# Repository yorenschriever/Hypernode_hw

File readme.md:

# HyperNode

HyperNode is a distribution node for 
[Hyperion](https://github.com/yorenschriever/Hyperion2). You can use this device to connect up to 8 led strips and 1 DMX universe. 

The device is based on the WT32-ETH01. The pcbs are made with AutoDesk Eagle. 

# BOM

|Amount|Name|Type|Value|Size|Price|Link|
|-|-|-|-|-|-|-|
|1|Controller||WT32-ETH01||||
|1|Line driver||74HCT245D|SO20W||
|1|DMX transceiver|MAX488||SOIC-8||
|2|Decoupling capacitor|Ceramic capacitor|100 nF|0603||
|10|Protection resistor|Thin film resistor|100 Ohm|0603||
|3|RJ45 Connectors|||||
|2|Resistor for led|Resistor|180 Ohm|0603|||
|2|Status and power led|SMD LED|Red|0603|||
|1|Power supply cap|Tantalum Capacitor|470 uF|D Type||
|1|Rectifier diode|||SMB||
|1|Step down module|||||
|1|JST XH connector M+F|2 Pin||||
|1|DC Barrel connector|2.1 x 5.5mm||||

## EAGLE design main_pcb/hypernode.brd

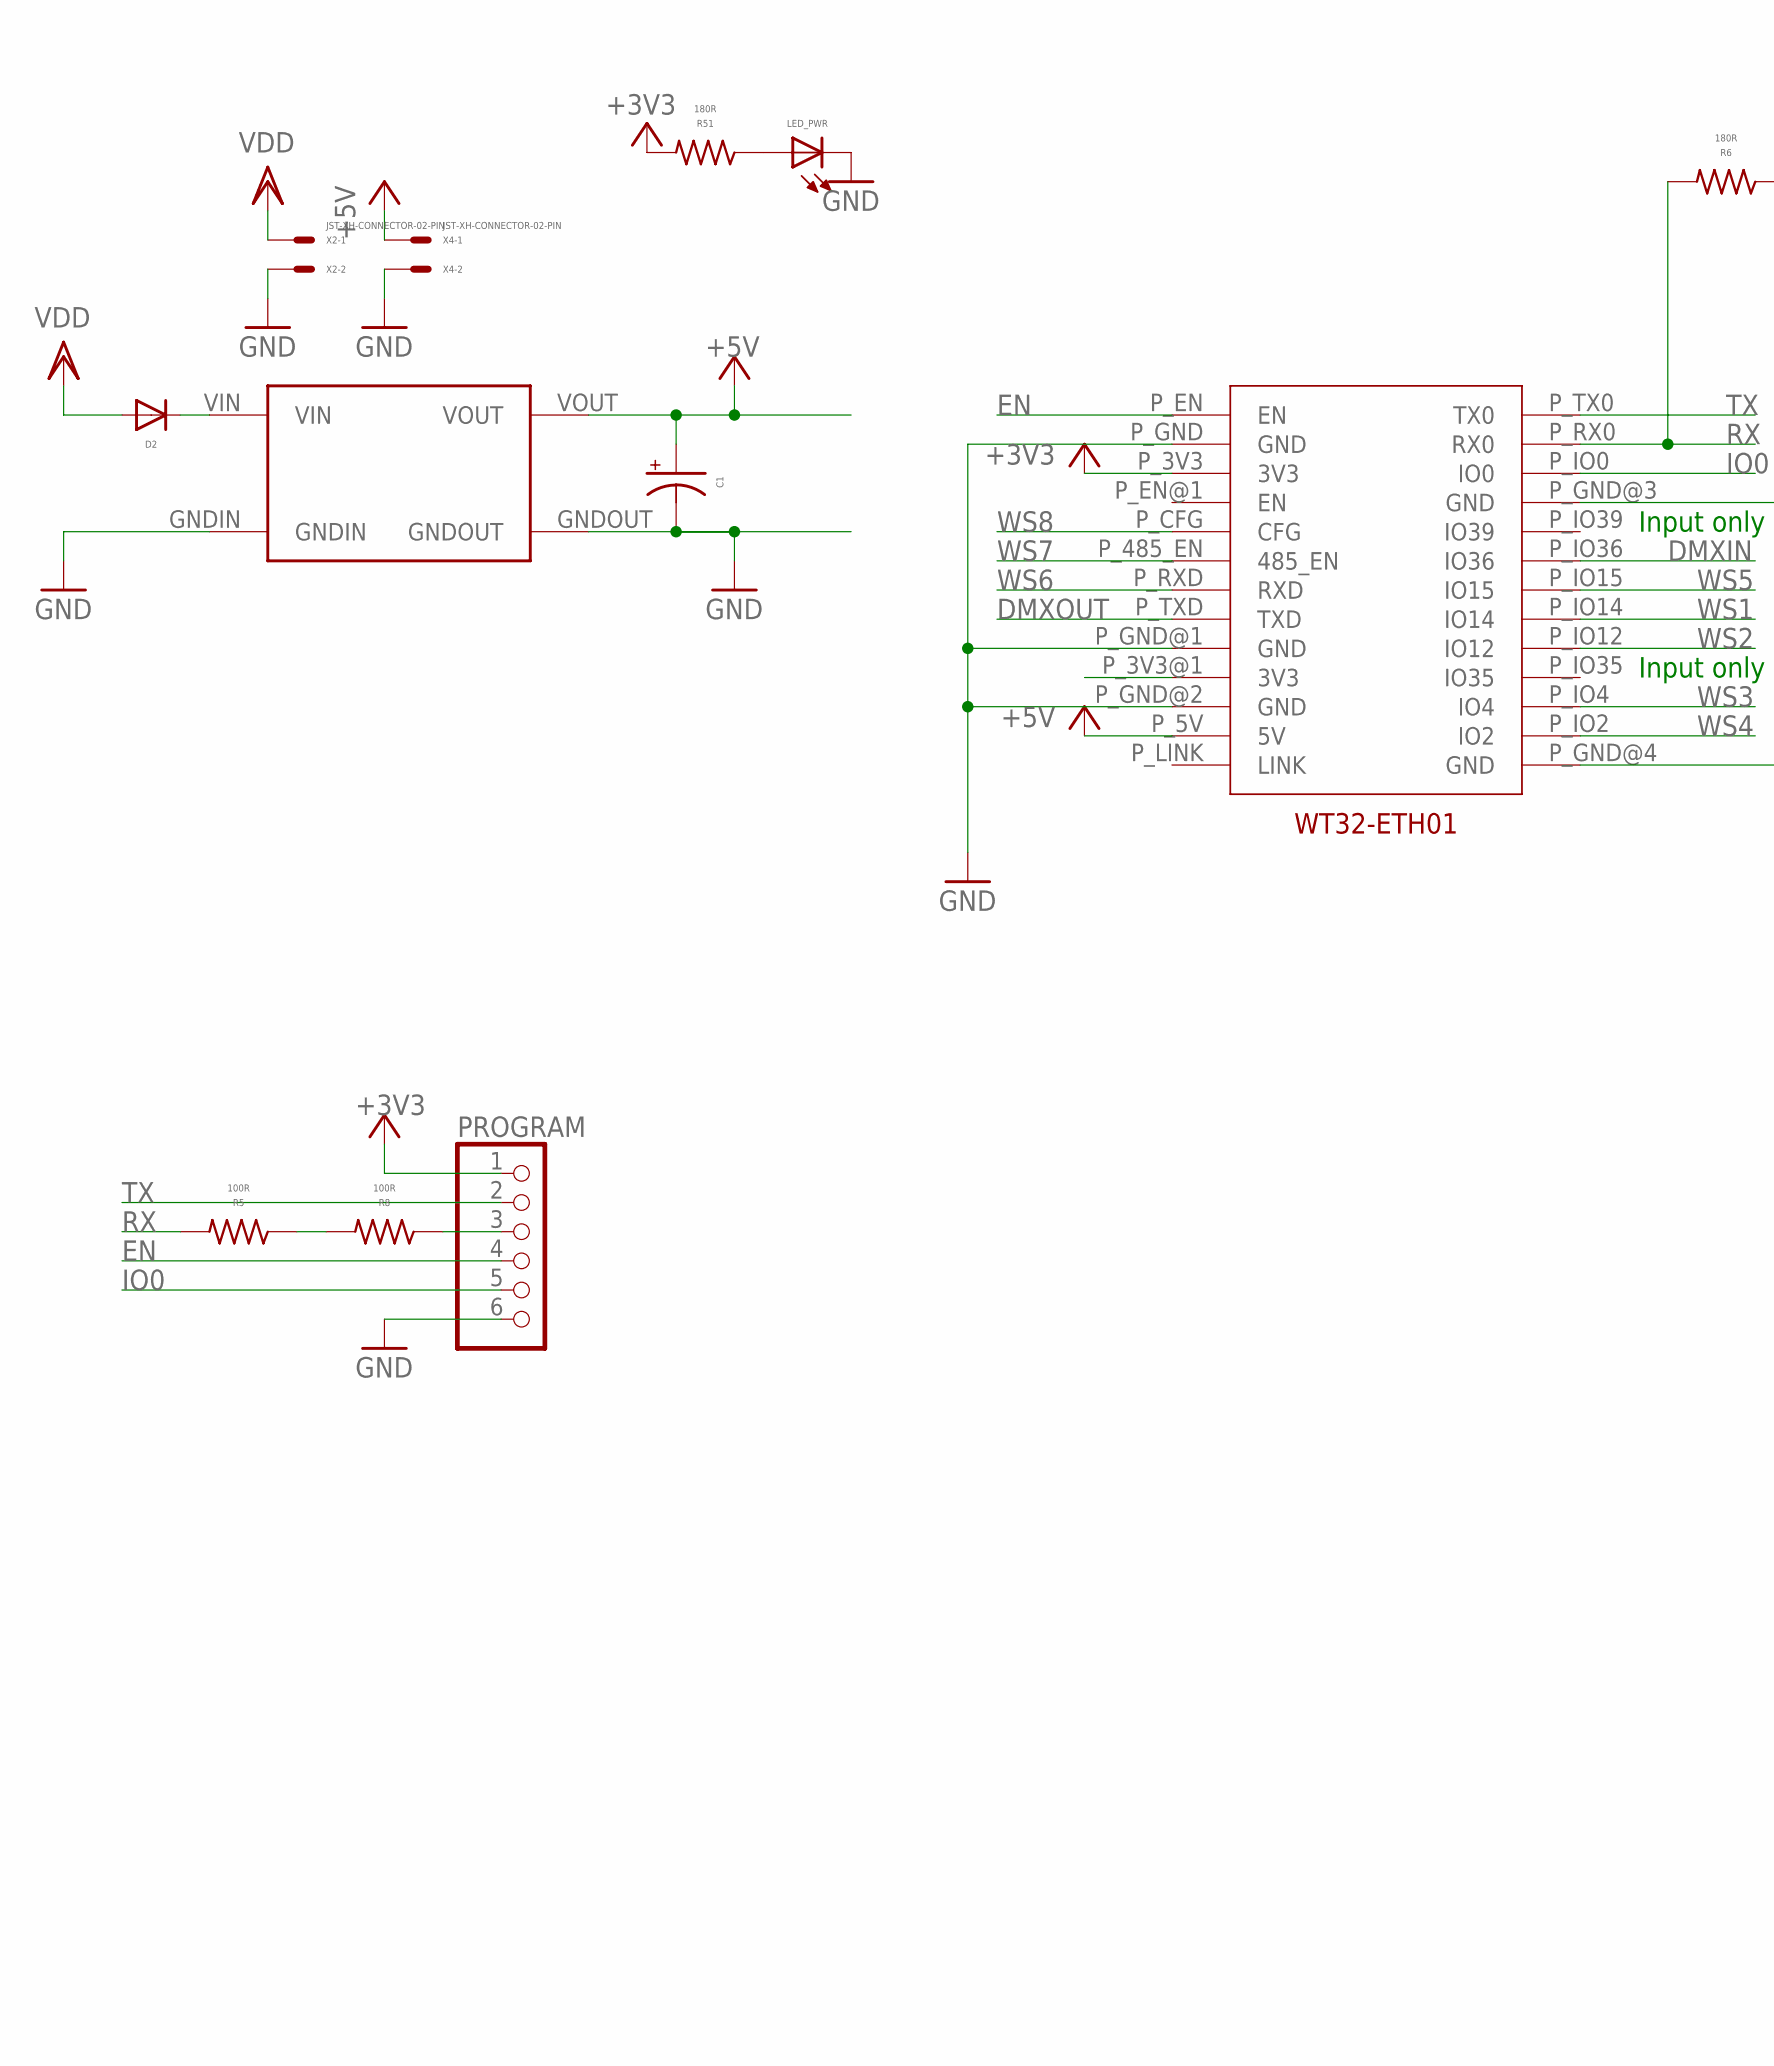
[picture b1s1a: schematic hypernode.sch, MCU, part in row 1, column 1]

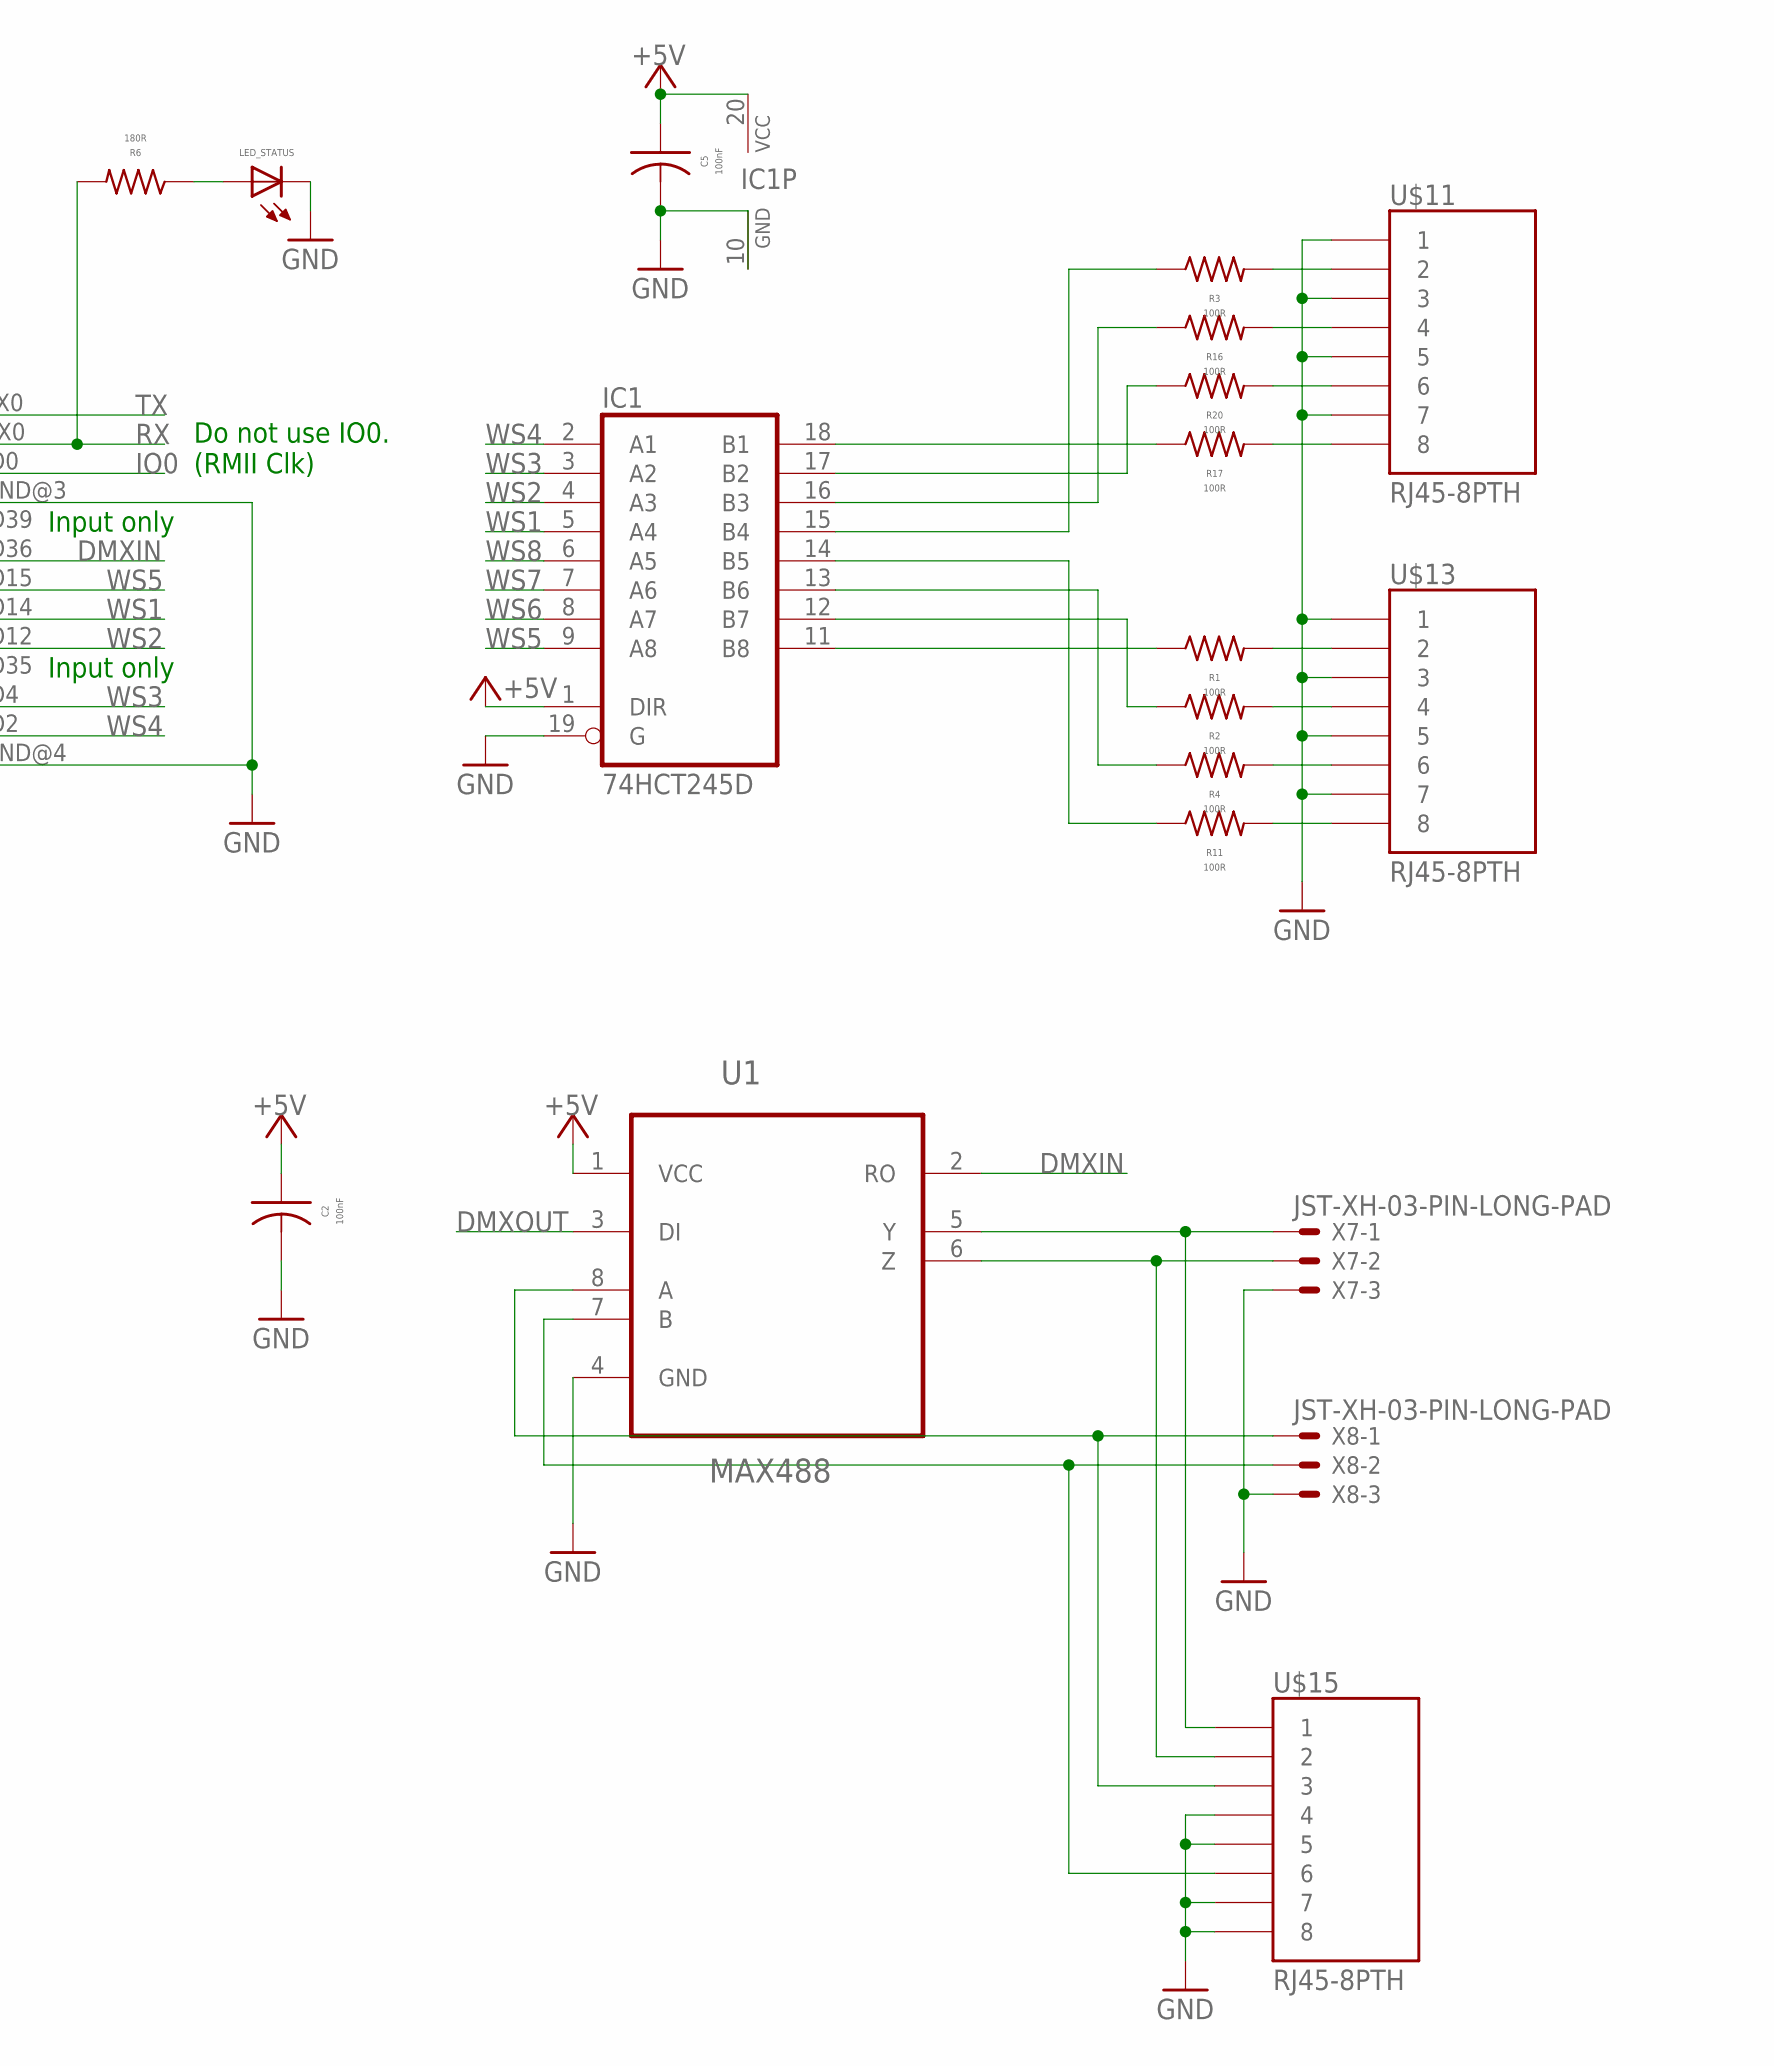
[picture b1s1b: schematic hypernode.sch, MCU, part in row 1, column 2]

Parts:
C1: CAPACITOR_SMC-D; RCL_SMC_D
C2, C5: 100nF; ADAFRUIT_C0603
D2: DIODE_SMB
IC1: 74HCT245D; SO20W
LED_PWR: LED0603; ADAFRUIT_CHIPLED_0603
LED_STATUS: LED0603; ADAFRUIT_CHIPLED_0603
PROGRAM: PINHD-1X6; 1X06
R1, R2, R3, R4, R5, R8, R11, R16, R17, R20: 100R; ADAFRUIT_R0603
R6, R51: 180R; ADAFRUIT_R0603
U1: MAX488; SOIC127P600X175-8N
U$3: STEPDOWNMODULE; STEPDOWN_MODULE
U$11, U$13, U$15: RJ45-8PTH; RJ45-8
U$17: WT32-ETH01WT32-ETH01-SMD; WT32-ETH01-SMD
X2, X4: JST-XH-CONNECTOR-02-PIN; REMBRANDT-ELECTRONICS---JST-XH-CONNECTORS-V1-0_JST-XH-02-PA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
X7, X8: JST-XH-03-PIN-LONG-PAD; JST-XH-03-PACKAGE-LONG-PAD

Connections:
+3V3: PROGRAM.1, R51.2, U$17.P_3V3 (3V3)
+5V: C1.+, C2.1, C5.1, IC1.1 (DIR), IC1.20 (VCC), U1.1 (VCC), U$3.VOUT, U$17.P_5V (5V), X4.1
DMXA: U1.8 (A), U$15.3, X8.1
DMXB: U1.7 (B), U$15.6, X8.2
DMXIN: U1.2 (RO), U$17.P_IO36 (IO36)
DMXOUT: U1.3 (DI), U$17.P_TXD (TXD)
DMXY: U1.5 (Y), U$15.1, X7.1
DMXZ: U1.6 (Z), U$15.2, X7.2
EN: PROGRAM.4, U$17.P_EN (EN)
GND: C1.-, C2.2, C5.2, IC1.10 (GND), IC1.19 (G), LED_PWR.C, LED_STATUS.C, PROGRAM.6, U1.4 (GND), U$3.GNDIN, U$3.GNDOUT, U$11.1, U$11.3, U$11.5, U$11.7, U$13.1, U$13.3, U$13.5, U$13.7, U$15.4, U$15.5, U$15.7, U$15.8, U$17.P_GND (GND), U$17.P_GND@1 (GND), U$17.P_GND@2 (GND), U$17.P_GND@3 (GND), U$17.P_GND@4 (GND), X2.2, X4.2, X7.3, X8.3
IO0: PROGRAM.5, U$17.P_IO0 (IO0)
unnamed: R5.1, R8.2
unnamed: LED_STATUS.A, R6.1
unnamed: R3.2, U$11.2
unnamed: D2.C, U$3.VIN
unnamed: R16.2, U$11.4
unnamed: R20.2, U$11.6
unnamed: R17.2, U$11.8
unnamed: R1.2, U$13.2
unnamed: IC1.18 (B1), R17.1
unnamed: R2.2, U$13.4
unnamed: IC1.17 (B2), R20.1
unnamed: IC1.16 (B3), R16.1
unnamed: IC1.15 (B4), R3.1
unnamed: IC1.14 (B5), R11.1
unnamed: IC1.13 (B6), R4.1
unnamed: IC1.12 (B7), R2.1
unnamed: IC1.11 (B8), R1.1
unnamed: R4.2, U$13.6
unnamed: R11.2, U$13.8
unnamed: PROGRAM.3, R8.1
unnamed: LED_PWR.A, R51.1
RX: R5.2, R6.2, U$17.P_RX0 (RX0)
TX: PROGRAM.2, U$17.P_TX0 (TX0)
VDD: D2.A, X2.1
WS1: IC1.5 (A4), U$17.P_IO14 (IO14)
WS2: IC1.4 (A3), U$17.P_IO12 (IO12)
WS3: IC1.3 (A2), U$17.P_IO4 (IO4)
WS4: IC1.2 (A1), U$17.P_IO2 (IO2)
WS5: IC1.9 (A8), U$17.P_IO15 (IO15)
WS6: IC1.8 (A7), U$17.P_RXD (RXD)
WS7: IC1.7 (A6), U$17.P_485_EN (485_EN)
WS8: IC1.6 (A5), U$17.P_CFG (CFG)

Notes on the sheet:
Do not use IO0. (RMII Clk)
Input only

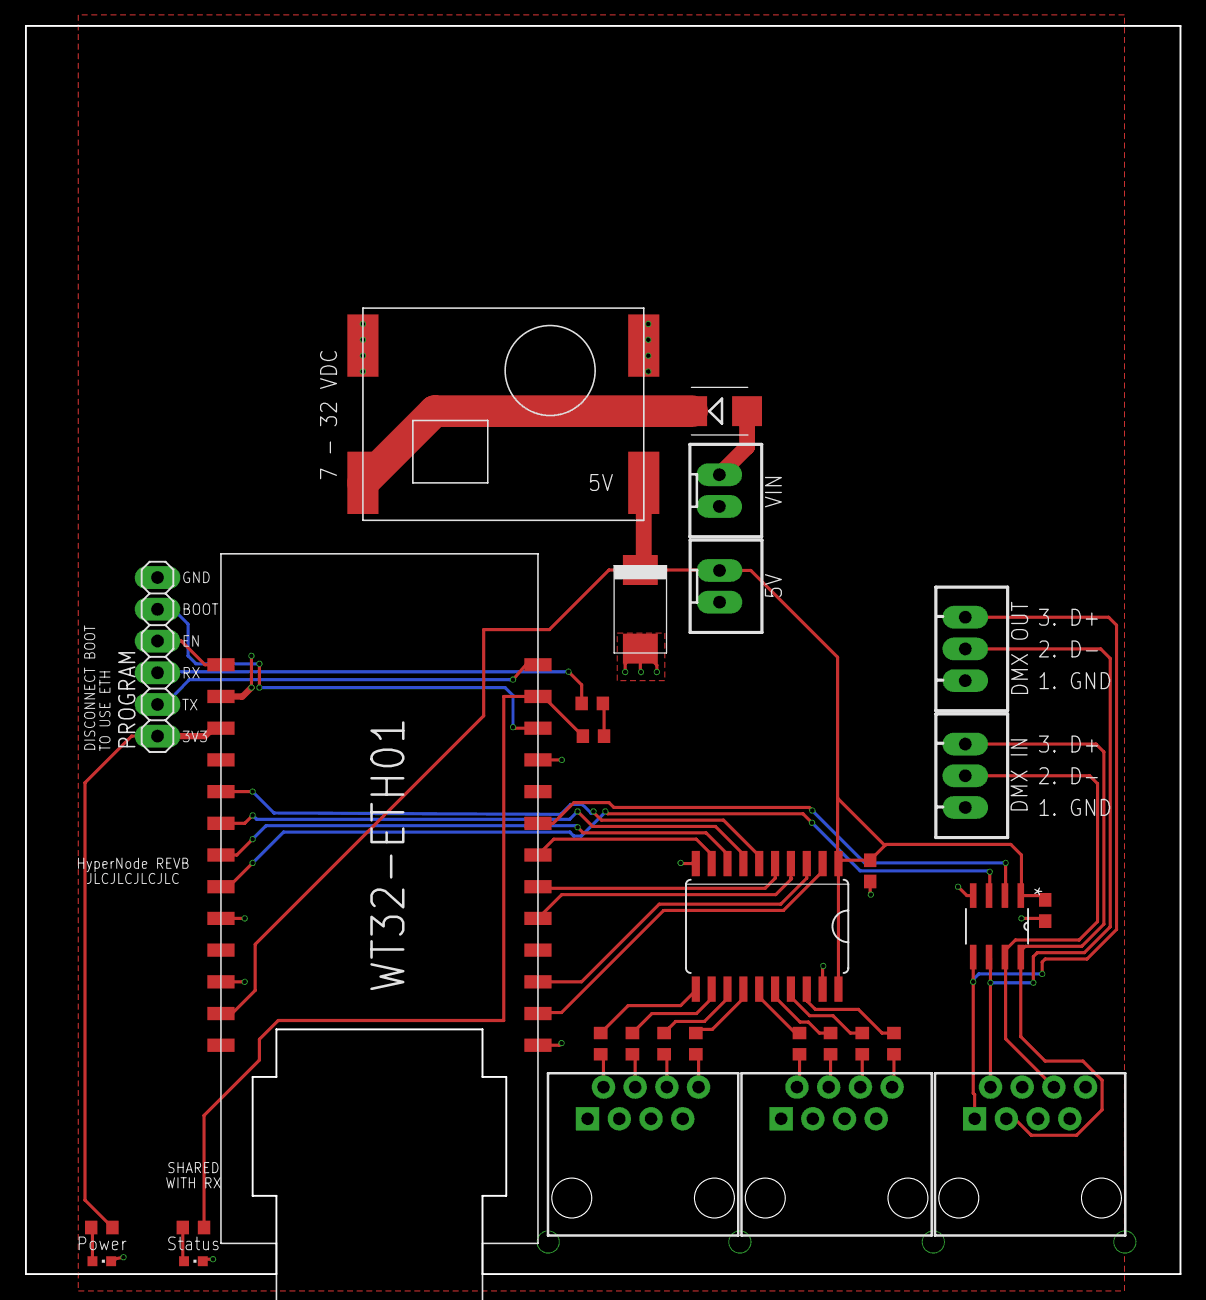
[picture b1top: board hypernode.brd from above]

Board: 2 copper layers, 92.5 x 100.0 mm, 31 parts (0 on the bottom side), 43 nets.

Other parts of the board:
U$4: MULTISCHRIEVERLOGO_SOLDERMASK

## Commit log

2024-12-16 commit copy of etherledesp32pcb_v22_fixes_after_revc as starting point
2024-12-16 remove unnecessary components from main pcb
2024-12-17 further cleanup and arrangement
2024-12-19 programmer
2024-12-20 routing
2024-12-21 copy fornt panel from hyperion
2024-12-21 front panel initial modifications
2024-12-22 measurements before origin move
2024-12-22 move origin
2024-12-22 align front panel
2024-12-22 rev A
2024-12-23 add ds_store to gitignore
2024-12-31 fix boot connetion
2024-12-31 move wrt32 away from ws2812 ports
2024-12-31 DRC and cleanup
2024-12-31 tented vias
2025-01-02 change rx resistor to 2x100r
2025-01-02 remove unnecessary pull down resistor
2025-01-02 feed power led from 3v3

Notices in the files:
parts and their libraries:
SparkFun-Connectors: Licensing: Creative Commons ShareAlike 4.0 International - https://creativecommons.org/licenses/by-sa/4.0
